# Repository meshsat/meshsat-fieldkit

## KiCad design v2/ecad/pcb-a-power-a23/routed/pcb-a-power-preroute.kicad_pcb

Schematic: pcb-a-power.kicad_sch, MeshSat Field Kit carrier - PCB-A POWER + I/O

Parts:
C1, C2: 47u 25V; C_1206_3216Metric
C3, C29, C30, C35, C36, C41, C42, C47, C48, C54, C120: 10u 25V 1210; C_1210_3225Metric
C4, C19: 1u; C_0603_1608Metric
C5, C26, C53, C57, C68, C75, C86, C98, C100, C102, C121: 10n; C_0603_1608Metric
C6, C58, C69, C76, C87: 100p; C_0603_1608Metric
C7, C59, C70, C77, C88: 47n; C_0603_1608Metric
C8, C60, C71, C78, C89: 4.7u; C_0805_2012Metric
C9, C10, C16, C17, C61, C62, C72, C73, C79, C80, C90, C91: 100n 25V; C_0603_1608Metric
C11, C12, C83, C84, C85: 10u 100V X7R 1210; C_1210_3225Metric
C13, C14, C15, C63, C64, C65, C66, C67, C74, C81, C82, C92, C108, C109, C110, C111, C116, C117, C118, C119: 10u 50V X7R 1210; C_1210_3225Metric
C18: 3.3u; C_0805_2012Metric
C20, C21, C22: 10u 35V 1210; C_1210_3225Metric
C23, C24, C25: 22u 25V 1210; C_1210_3225Metric
C27: 1n; C_0603_1608Metric
C28, C34, C40, C46, C52, C93, C95, C99, C101, C103, C104, C106, C107, C122: 100n; C_0603_1608Metric
C31, C32, C33, C37, C38, C39, C43, C44, C45, C49, C50, C51, C55, C56: 22u 10V X7R 1210; C_1210_3225Metric
C94: 220n; C_0603_1608Metric
C96, C97: 330p; C_0603_1608Metric
C112, C113, C114, C115: 3.3n; C_0603_1608Metric
D1: SMCJ18A (VBAT clamp); D_SMC; LCSC C374030
D2: SMCJ40A (VIN_RAW clamp behind E6's filter: 40 V s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; D_SMC; LCSC C224052
D3: SMBJ5.0A; D_SMB
D4: SMBJ18A (VBUS clamp at the outlet); D_SMB
F1: 25 A mini blade (Keystone 3568 holder): pack node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; Fuseholder_Blade_Mini_Keystone_3568
J_5V_DEV: USB device rail to B16 (JST-VH): + -; JST_VH_B2P-VH_1x02_P3.96mm_Vertical; LCSC C274411
J_5V_S1: slot 1 5.1 V rail to B16 (JST-VH, 16 AWG): + -; JST_VH_B2P-VH_1x02_P3.96mm_Vertical; LCSC C274411
J_5V_S2: slot 2 5.1 V rail to B16 (JST-VH, 16 AWG): + -; JST_VH_B2P-VH_1x02_P3.96mm_Vertical; LCSC C274411
J_5V_S3: slot 3 5.1 V rail to B16 (JST-VH, 16 AWG): + -; JST_VH_B2P-VH_1x02_P3.96mm_Vertical; LCSC C274411
J_54V: 54 V to the PoE injector on B16 (JST-VH): + -; JST_VH_B2P-VH_1x02_P3.96mm_Vertical; LCSC C274411
J_AB1: A-B interconnect (IDC 2x13, top side) to B16's un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; IDC-Header_2x13_P2.54mm_Vertical_NarrowPad
J_AB2: A-B wall-port ribbon (IDC 2x5): the wall USB pair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; IDC-Header_2x05_P2.54mm_Vertical_NarrowPad
J_BM1, J_BM2, J_BM3, J_BM4, J_BM5, J_BM6, J_BM7, J_BM8, J_BM9, J_BM10, J_BM11: SMP-MAX slide-on receptacle R222M00720 (underside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; Radiall_SMPMAX_R222M00720
J_CN1, J_CN2, J_CN3, J_CN4: 9 A spring pin, pack return (Mill-Max 0858 class,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; Mill-Max_0858_power_pin
J_CP1, J_CP2, J_CP3, J_CP4: 9 A spring pin, CELL+ (Mill-Max 0858 class, dock 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; Mill-Max_0858_power_pin
J_DOCK: spring pins to the dock block (2x6, Preci-Dip 813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; PogoPins_2x6
J_HEAT: JST-XH 1x2 socket: the heater mat under the 2590 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; JST_XH_B2B-XH-A_1x02_P2.50mm_Vertical; LCSC C265283
J_HF: 12.0 V to the QMX HF unit in its lid tray (JST-VH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; JST_VH_B2P-VH_1x02_P3.96mm_Vertical; LCSC C274411
J_MAINSW: JST-XH 1x2 socket: the MAIN button lead from the 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; JST_XH_B2B-XH-A_1x02_P2.50mm_Vertical; LCSC C265283
J_MEZZ1: D8 mezzanine harness (IDC 2x8): its USB pair, the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; IDC-Header_2x08_P2.54mm_Vertical_NarrowPad
J_MEZZ_PWR1: D8 mezzanine 5 V (JST-VH): + -; JST_VH_B2P-VH_1x02_P3.96mm_Vertical; LCSC C274411
J_MON: monitor supply lead to the Xenarc (JST-VH): + -; JST_VH_B2P-VH_1x02_P3.96mm_Vertical; LCSC C274411
J_PA: 13.8 V to the PA module on the face plate (JST-VH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; JST_VH_B2P-VH_1x02_P3.96mm_Vertical; LCSC C274411
J_PRE1: pre-charge pin, longer, mates first (32.24 AX); Mill-Max_0858_power_pin
J_RF1, J_RF2, J_RF3, J_RF4, J_RF5, J_RF6, J_RF7, J_RF8, J_RF9, J_RF10, J_RF11: SMA jack, Amphenol 132134-11 vertical (pigtail to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; SMA_Amphenol_132134-11_Vertical; LCSC C3174425
J_USBC_OUT: wall USB-C outlet, power side (pigtail header): V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; PinHeader_1x05_P2.54mm_Vertical
J_USBW: JST-PH 1x4 socket: the wall USB-C data pair to B1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; JST_PH_B4B-PH-K_1x04_P2.00mm_Vertical; LCSC C131334
L1: 10uH XAL1010-103ME (Isat 14 A); L_Coilcraft_XAL1010-XXX
L2: 3.3uH XAL6030-332ME (Isat 12.2 A); L_Coilcraft_XAL6060-XXX
L3, L4, L5, L6: 4.7uH XAL6060-472ME (Isat 11 A); L_Coilcraft_XAL6060-XXX
L7: 4.7uH XAL4030-472ME; L_Coilcraft_XAL4030-XXX
L8: 6.8uH XAL1010-682ME (Isat 17 A); L_Coilcraft_XAL1010-XXX
L9, L11: 6.8uH XAL1010-682ME; L_Coilcraft_XAL1010-XXX
L10: 22uH XAL1010-223ME (Isat 9 A); L_Coilcraft_XAL1010-XXX
Q1: 2N7002: panel controller high = pull KILL low = p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; SOT-23
Q2, Q3, Q4, Q5, Q17, Q18, Q19, Q20: CSD19532Q5B 100 V N-FET (4.6 mOhm at VGS 6 V, Pow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; PowerPAK_SO-8_Single; LCSC C473333
Q6: 2N7002: CHG_INHIBIT high = ILIM_HIZ low = charger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; SOT-23
Q7, Q8, Q9, Q10, Q11, Q12, Q13, Q14, Q15, Q16, Q21, Q22, Q23, Q24, Q25, Q26: CSD18510Q5B 40 V N-FET; PowerPAK_SO-8_Single
Q27: CSD18510Q5B 40 V N-FET (VBUS switch); PowerPAK_SO-8_Single
R1: 10R 2W 2512; R_2512_6332Metric
R2, R3, R4, R5, R13, R21, R30, R34, R38, R42, R57, R73, R102, R103, R104, R111, R112, R113, R114, R116, R118, R123, R128, R143, R145: 100k; R_0603_1608Metric
R6: 240k 1%; R_0603_1608Metric
R7, R15, R29, R33, R37, R41, R49, R51, R59, R61, R67, R75, R125, R134: 10k 1%; R_0603_1608Metric
R8, R52, R62, R68, R78: 40.2k (300 kHz); R_0603_1608Metric
R9, R53, R63, R69, R79: 30k (slope); R_0603_1608Metric
R10, R22, R23, R25, R44, R54, R64, R70, R80, R91, R95, R99, R110, R117, R142: 10k; R_0603_1608Metric
R11, R65, R81, R138: 10mOhm 1% 2512 (ISNS); R_2512_6332Metric
R12, R56, R122, R127: 5mOhm 1% 2512 (CS); R_2512_6332Metric
R14, R58, R74, R124, R133: 62k 1%; R_0603_1608Metric
R16: 10mOhm 1% 2512 (RAC, input current sense); R_2512_6332Metric
R17: 5mOhm 1% 2512 (RSR, charge current sense); R_2512_6332Metric
R18, R146, R147, R148, R149: 10R; R_0603_1608Metric
R19: 16.5k 1%; R_0603_1608Metric
R20: 34.8k 1%; R_0603_1608Metric
R24: 10k (PSYS load); R_0603_1608Metric
R26: 60.4k 1% (CELL_BATPRESZ: 4S per Table, from VDDA); R_0603_1608Metric
R27: 40.2k 1%; R_0603_1608Metric
R28, R32, R36, R40: 53.6k 1%; R_0603_1608Metric
R31, R35, R39, R43: 5mOhm 1% 2512 (shunt); R_2512_6332Metric
R45, R46, R47, R115: 68k (RT: 500 kHz); R_0603_1608Metric
R48: 31.6k 1%; R_0603_1608Metric
R50: 162k 1%; R_0603_1608Metric
R55: 2mOhm 1% 2512 (ISNS); R_2512_6332Metric
R60: 140k 1%; R_0603_1608Metric
R66: 665k 1%; R_0603_1608Metric
R71: 20mOhm 1% 2512 (ISNS); R_2512_6332Metric
R72: 10mOhm 1% 2512 (CS); R_2512_6332Metric
R76: 105k 1%; R_0603_1608Metric
R77: 20k 1% (R_FBL); R_0603_1608Metric
R90: 750R 1% (ILM: 1.2 A); R_0603_1608Metric
R92, R96, R100: 100k 1%; R_0603_1608Metric
R93, R97, R101: 10k 1% (OVLO); R_0603_1608Metric
R94: 909R 1% (ILM: 1.0 A); R_0603_1608Metric
R98: 453R 1% (ILM: 2.0 A); R_0603_1608Metric
R119, R120, R121, R126, R135: 100k (MODE: CCM); R_0603_1608Metric
R129, R130, R131, R132: 22k; R_0603_1608Metric
R136: 21.0k 1% (R_FBL2: 9 V when CTL2 is low); R_0603_1608Metric
R137: 14.0k 1% (R_FBL1: 15 V when CTL1 is low too); R_0603_1608Metric
R139: 43R 1W 2512 (DSCG); R_2512_6332Metric
R140: 1M (GD to VPWR, 9.1.3); R_0603_1608Metric
R141: 698k; R_0603_1608Metric
TP3: EXP2_SP3; TestPoint_Pad_D1.5mm
TP4: EXP2_SP4; TestPoint_Pad_D1.5mm
TP5: EXP2_SP5; TestPoint_Pad_D1.5mm
TP6: EXP2_SP6; TestPoint_Pad_D1.5mm
TP7: EXP2_SP7; TestPoint_Pad_D1.5mm
TP8: EXP2_SP8; TestPoint_Pad_D1.5mm
TP9: VBAT; TestPoint_Pad_D1.5mm
TP10: GND; TestPoint_Pad_D1.5mm
TP11: +3V3; TestPoint_Pad_D1.5mm
TP12: VBUS20; TestPoint_Pad_D1.5mm
TP13: VIN_RAW; TestPoint_Pad_D1.5mm
TP14: CELL+; TestPoint_Pad_D1.5mm
TP15: EMCON_HW; TestPoint_Pad_D1.5mm
TP16: RAIL_EN; TestPoint_Pad_D1.5mm
TP17: SDA; TestPoint_Pad_D1.5mm
TP18: SCL; TestPoint_Pad_D1.5mm
TP19: IADPT; TestPoint_Pad_D1.5mm
TP20: IBAT; TestPoint_Pad_D1.5mm
TP21: DOCK_SPARE; TestPoint_Pad_D1.5mm
TP22: REGN; TestPoint_Pad_D1.5mm
TP23: EXP2_SPA; TestPoint_Pad_D1.5mm
TP24: EXP2_SPB; TestPoint_Pad_D1.5mm
TP25: EXP2_SPC; TestPoint_Pad_D1.5mm
TP26: EXP2_SPD; TestPoint_Pad_D1.5mm
TP27: AB_SPARE; TestPoint_Pad_D1.5mm
U1: LTC2954CTS8-1 push-button on/off controller; TSOT-23-8; LCSC C683782
U2: LM5176PWPR buck-boost controller, VBUS20 from VIN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; HTSSOP-28-1EP_4.4x9.7mm_P0.65mm_EP2.85x5.4mm; LCSC C442493
U3: BQ25731RSNR 1 to 5 cell buck-boost charger, 4S fr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; QFN-32-1EP_4x4mm_P0.4mm_EP2.65x2.65mm; LCSC C2871872
U4: AP64500SP-13 5 A buck, 5.1 V rail +5V_S1; SOIC-8-1EP_3.9x4.9mm_P1.27mm_EP2.29x3mm; LCSC C2070920
U5: AP64500SP-13 5 A buck, 5.1 V rail +5V_S2; SOIC-8-1EP_3.9x4.9mm_P1.27mm_EP2.29x3mm; LCSC C2070920
U6: AP64500SP-13 5 A buck, 5.1 V rail +5V_S3; SOIC-8-1EP_3.9x4.9mm_P1.27mm_EP2.29x3mm; LCSC C2070920
U7: AP64500SP-13 5 A buck, 5.1 V rail +5V_DEV; SOIC-8-1EP_3.9x4.9mm_P1.27mm_EP2.29x3mm; LCSC C2070920
U8: INA226 rail monitor +5V_S1; VSSOP-10_3x3mm_P0.5mm; LCSC C49851
U9: INA226 rail monitor +5V_S2; VSSOP-10_3x3mm_P0.5mm; LCSC C49851
U10: INA226 rail monitor +5V_S3; VSSOP-10_3x3mm_P0.5mm; LCSC C49851
U11: INA226 rail monitor +5V_DEV; VSSOP-10_3x3mm_P0.5mm; LCSC C49851
U12: TPS62933DRLR 3 A buck, 3.3 V logic; SOT-583-8; LCSC C3200405
U13: LM5176PWPR buck-boost controller, +13V8_PA from V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; HTSSOP-28-1EP_4.4x9.7mm_P0.65mm_EP2.85x5.4mm; LCSC C442493
U14: INA226 PA rail monitor (0x46); VSSOP-10_3x3mm_P0.5mm; LCSC C49851
U15: LM5176PWPR buck-boost controller, +12V_HF from VB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; HTSSOP-28-1EP_4.4x9.7mm_P0.65mm_EP2.85x5.4mm; LCSC C442493
U16: LM5176PWPR buck-boost controller, +54V_POE from V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; HTSSOP-28-1EP_4.4x9.7mm_P0.65mm_EP2.85x5.4mm; LCSC C442493
U17: INA226 PoE rail monitor (0x47); VSSOP-10_3x3mm_P0.5mm; LCSC C49851
U18: TPS25740ARGER USB-C PD source controller, 45 W ou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; QFN-24-1EP_4x4mm_P0.5mm_EP2.5x2.5mm; LCSC C544309
U19: LM5176PWPR buck-boost controller, PD_VPWR from VB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; HTSSOP-28-1EP_4.4x9.7mm_P0.65mm_EP2.85x5.4mm; LCSC C442493
U21: TPS259631DDAR eFuse VBAT -> VMON (750R 1% (ILM: 1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; SOIC-8-1EP_3.9x4.9mm_P1.27mm_EP2.29x3mm; LCSC C2155778
U22: TPS259631DDAR eFuse VBAT -> VHEAT (909R 1% (ILM: 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; SOIC-8-1EP_3.9x4.9mm_P1.27mm_EP2.29x3mm; LCSC C2155778
U23: TPS259631DDAR eFuse +5V_DEV -> +5V_D8 (453R 1% (I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; SOIC-8-1EP_3.9x4.9mm_P1.27mm_EP2.29x3mm; LCSC C2155778
U26: SN74LVC08APWR quad AND: EMCON gates for the PA ra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; TSSOP-14_4.4x5mm_P0.65mm; LCSC C465737
U27: PCA9555PW (0x21): enables and status; TSSOP-24_4.4x7.8mm_P0.65mm; LCSC C2864778
U28: PCA9555PW (0x24): power-good lines, spares; TSSOP-24_4.4x7.8mm_P0.65mm; LCSC C2864778
U29: USBLC6-2SC6; SOT-23-6; LCSC C7519

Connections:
+3V3: C55.1, C56.1, C104.1, C106.1, C107.1, D3.1 (A1), J_MEZZ1.13, L7.2, R3.2, R13.2, R22.2, R23.2, R44.2, R48.1, R57.2, R73.2, R91.2, R95.2, R99.2, R110.2, R117.2, R123.2, R128.2, R142.2, TP11.1, U8.6 (+3V3), U9.2 (+3V3), U9.6 (+3V3), U10.1 (+3V3), U10.6 (+3V3), U11.1 (+3V3), U11.2 (+3V3), U11.6 (+3V3), U14.1 (+3V3), U14.6 (+3V3), U17.1 (+3V3), U17.6 (+3V3), U26.14 (+3V3), U27.21 (A0), U27.24 (VDD), U28.3 (A2), U28.24 (VDD)
/+5V_D8: J_MEZZ_PWR1.1, U23.5 (+5V_D8)
/+5V_DEV: C49.1, C50.1, C51.1, C103.1, J_5V_DEV.1, R40.1, R43.2, R100.1, U11.8 (+5V_DEV), U11.9 (+5V_DEV), U18.17 (+5V_DEV), U23.4 (+5V_DEV), U29.5 (VBUS)
/+5V_S1: C31.1, C32.1, C33.1, J_5V_S1.1, R28.1, R31.2, U8.8 (+5V_S1), U8.9 (+5V_S1)
/+5V_S2: C37.1, C38.1, C39.1, J_5V_S2.1, R32.1, R35.2, U9.8 (+5V_S2), U9.9 (+5V_S2)
/+5V_S3: C43.1, C44.1, C45.1, J_5V_S3.1, R36.1, R39.2, U10.8 (+5V_S3), U10.9 (+5V_S3)
/+12V_HF: C109.1, C110.1, C111.1, J_HF.1, R60.1, R65.2, U15.12 (+12V_HF), U15.13 (+12V_HF), U15.24 (+12V_HF)
/+13V8_PA: C65.1, C66.1, C67.1, J_PA.1, R50.1, R55.2, U13.12 (+13V8_PA), U13.13 (+13V8_PA), U13.24 (+13V8_PA), U14.8 (+13V8_PA), U14.9 (+13V8_PA)
/+54V_POE: C83.1, C84.1, C85.1, J_54V.1, R66.1, R71.2, U16.12 (+54V_POE), U16.13 (+54V_POE), U17.9 (+54V_POE)
/AB_SPARE: J_MEZZ1.16, TP27.1
/B33_BST: C52.1, U12.6 (B33_BST)
/B33_FB: R48.2, R49.1, U12.8 (B33_FB)
/B33_SS: C53.1, U12.7 (B33_SS)
/B33_SW: C52.2, L7.1, U12.5 (B33_SW)
/CHG_ILIM: Q6.3 (D), R19.2, R20.1, U3.6 (CHG_ILIM)
/CHG_INHIBIT: Q6.1 (G), R21.1, U27.4 (IO0_0)
/CHRG_OK: R22.1, U3.4 (CHRG_OK), U27.13 (IO1_0)
/CH_BTST1: C16.1, U3.30 (CH_BTST1)
/CH_BTST2: C17.1, U3.25 (CH_BTST2)
/CH_CELL: R26.2, R27.1, U3.18 (CH_CELL)
/CH_COMP1: R25.1, U3.16 (CH_COMP1)
/CH_COMP1C: C26.1, R25.2
/CH_COMP2: C27.1, U3.17 (CH_COMP2)
/CH_HIDRV1: Q7.4 (CH_HIDRV1), U3.31 (CH_HIDRV1)
/CH_HIDRV2: Q10.4 (CH_HIDRV2), U3.24 (CH_HIDRV2)
/CH_LODRV1: Q8.4 (CH_LODRV1), U3.29 (CH_LODRV1)
/CH_LODRV2: Q9.4 (CH_LODRV2), U3.26 (CH_LODRV2)
/CH_SW1: C16.2, L2.1, Q7.1 (CH_SW1), Q7.2 (CH_SW1), Q7.3 (CH_SW1), Q8.5 (CH_SW1), U3.32 (CH_SW1)
/CH_SW2: C17.2, L2.2, Q9.5 (CH_SW2), Q10.1 (CH_SW2), Q10.2 (CH_SW2), Q10.3 (CH_SW2), U3.23 (CH_SW2)
/CH_VDDA: C19.1, R18.2, R26.1, U3.7 (CH_VDDA)
/D8_EN: R113.1, U23.3 (D8_EN), U27.7 (IO0_3)
/D8_FLT: R99.1, U23.6 (D8_FLT), U27.17 (IO1_4)
/DEV_EN: R42.1, U7.3 (DEV_EN), U27.11 (IO0_7)
/DOCK_SPARE: J_DOCK.12, TP21.1, U27.18 (IO1_5)
/EMCON_HW: J_AB1.15, R102.1, TP15.1, U26.1 (EMCON_HW), U26.4 (EMCON_HW)
/EXP2_SP3: TP3.1, U28.15 (IO1_2)
/EXP2_SP4: TP4.1, U28.16 (IO1_3)
/EXP2_SP5: TP5.1, U28.17 (IO1_4)
/EXP2_SP6: TP6.1, U28.18 (IO1_5)
/EXP2_SP7: TP7.1, U28.19 (IO1_6)
/EXP2_SP8: TP8.1, U28.20 (IO1_7)
/EXP2_SPA: TP23.1, U28.4 (IO0_0)
/EXP2_SPB: TP24.1, U28.5 (IO0_1)
/EXP2_SPC: TP25.1, U28.6 (IO0_2)
/EXP2_SPD: TP26.1, U28.7 (IO0_3)
/EXP_INT: J_AB1.13, J_MEZZ1.12, R110.1, U27.1 (~INT), U28.1 (~INT)
/FE_BOOT1: C9.1, U2.26 (FE_BOOT1)
/FE_BOOT2: C10.1, U2.20 (FE_BOOT2)
/FE_COMP: C6.1, R10.1, U2.9 (FE_COMP)
/FE_COMPC: C5.1, R10.2
/FE_CS: Q3.1 (FE_CS), Q3.2 (FE_CS), Q3.3 (FE_CS), Q4.1 (FE_CS), Q4.2 (FE_CS), Q4.3 (FE_CS), R12.1, U2.16 (FE_CS)
/FE_EN: R14.2, R15.1, U2.1 (FE_EN)
/FE_FB: R6.2, R7.1, U2.11 (FE_FB)
/FE_HDRV1: Q2.4 (FE_HDRV1), U2.27 (FE_HDRV1)
/FE_HDRV2: Q5.4 (FE_HDRV2), U2.19 (FE_HDRV2)
/FE_LDRV1: Q3.4 (FE_LDRV1), U2.25 (FE_LDRV1)
/FE_LDRV2: Q4.4 (FE_LDRV2), U2.21 (FE_LDRV2)
/FE_MODE: R119.1, U2.4 (FE_MODE)
/FE_OUT: Q5.5 (FE_OUT), R11.1, U2.14 (FE_OUT)
/FE_PGOOD: R13.1, U2.17 (FE_PGOOD), U27.20 (IO1_7)
/FE_RT: R8.1, U2.6 (FE_RT)
/FE_SLOPE: R9.1, U2.7 (FE_SLOPE)
/FE_SS: C7.1, U2.8 (FE_SS)
/FE_SW1: C9.2, L1.1, Q2.1 (FE_SW1), Q2.2 (FE_SW1), Q2.3 (FE_SW1), Q3.5 (FE_SW1), U2.28 (FE_SW1)
/FE_SW2: C10.2, L1.2, Q4.5 (FE_SW2), Q5.1 (FE_SW2), Q5.2 (FE_SW2), Q5.3 (FE_SW2), U2.18 (FE_SW2)
/FE_VCC: C8.1, R119.2, U2.23 (FE_VCC)
/HEAT_EN: R112.1, U22.3 (HEAT_EN), U27.6 (IO0_2)
/HEAT_FLT: R95.1, U22.6 (HEAT_FLT), U27.16 (IO1_3)
/HF_BOOT1: C72.1, U15.26 (HF_BOOT1)
/HF_BOOT2: C73.1, U15.20 (HF_BOOT2)
/HF_COMP: C69.1, R64.1, U15.9 (HF_COMP)
/HF_COMPC: C68.1, R64.2
/HF_CS: Q16.1 (HF_CS), Q16.2 (HF_CS), Q16.3 (HF_CS), Q23.1 (HF_CS), Q23.2 (HF_CS), Q23.3 (HF_CS), R122.1, U15.16 (HF_CS)
/HF_EN: R124.1, R124.2, R125.1, U15.1 (HF_EN), U26.6 (HF_EN)
/HF_FB: R60.2, R61.1, U15.11 (HF_FB)
/HF_HDRV1: Q15.4 (HF_HDRV1), U15.27 (HF_HDRV1)
/HF_HDRV2: Q24.4 (HF_HDRV2), U15.19 (HF_HDRV2)
/HF_LDRV1: Q16.4 (HF_LDRV1), U15.25 (HF_LDRV1)
/HF_LDRV2: Q23.4 (HF_LDRV2), U15.21 (HF_LDRV2)
/HF_MODE: R126.1, U15.4 (HF_MODE)
/HF_OUT: Q24.5 (HF_OUT), R65.1, U15.14 (HF_OUT)
/HF_PGOOD: R123.1, U15.17 (HF_PGOOD), U28.10 (IO0_6)
/HF_RT: R62.1, U15.6 (HF_RT)
/HF_SLOPE: R63.1, U15.7 (HF_SLOPE)
/HF_SS: C70.1, U15.8 (HF_SS)
/HF_SW1: C72.2, L9.1, Q15.1 (HF_SW1), Q15.2 (HF_SW1), Q15.3 (HF_SW1), Q16.5 (HF_SW1), U15.28 (HF_SW1)
/HF_SW2: C73.2, L9.2, Q23.5 (HF_SW2), Q24.1 (HF_SW2), Q24.2 (HF_SW2), Q24.3 (HF_SW2), U15.18 (HF_SW2)
/HF_SW_EN: R104.1, U26.5 (HF_SW_EN), U27.10 (IO0_6)
/HF_VCC: C71.1, R126.2, U15.23 (HF_VCC)
/IADPT: TP19.1, U3.8 (IADPT)
/IBAT: TP20.1, U3.9 (IBAT)
/INA_ALERT: R44.1, U8.3 (INA_ALERT), U9.3 (INA_ALERT), U10.3 (INA_ALERT), U11.3 (INA_ALERT), U14.3 (INA_ALERT), U17.3 (INA_ALERT), U27.19 (IO1_6)
/KILL: Q1.3 (D), R4.1, U1.8 (KILL)
/MAIN_PB: J_MAINSW.1, U1.2 (MAIN_PB)
/MON_EN: R111.1, U21.3 (MON_EN), U27.5 (IO0_1)
/MON_FLT: R91.1, U21.6 (MON_FLT), U27.15 (IO1_2)
/PA_BOOT1: C61.1, U13.26 (PA_BOOT1)
/PA_BOOT2: C62.1, U13.20 (PA_BOOT2)
/PA_COMP: C58.1, R54.1, U13.9 (PA_COMP)
/PA_COMPC: C57.1, R54.2
/PA_CS: Q12.1 (PA_CS), Q12.2 (PA_CS), Q12.3 (PA_CS), Q13.1 (PA_CS), Q13.2 (PA_CS), Q13.3 (PA_CS), R56.1, U13.16 (PA_CS)
/PA_EN: J_MEZZ1.9, R58.1, R58.2, R59.1, U13.1 (PA_EN), U26.3 (PA_EN)
/PA_FB: R50.2, R51.1, U13.11 (PA_FB)
/PA_HDRV1: Q11.4 (PA_HDRV1), U13.27 (PA_HDRV1)
/PA_HDRV2: Q14.4 (PA_HDRV2), U13.19 (PA_HDRV2)
/PA_LDRV1: Q12.4 (PA_LDRV1), U13.25 (PA_LDRV1)
/PA_LDRV2: Q13.4 (PA_LDRV2), U13.21 (PA_LDRV2)
/PA_MODE: R120.1, U13.4 (PA_MODE)
/PA_OUT: Q14.5 (PA_OUT), R55.1, U13.14 (PA_OUT), U14.10 (PA_OUT)
/PA_PGOOD: R57.1, U13.17 (PA_PGOOD), U28.8 (IO0_4)
/PA_RT: R52.1, U13.6 (PA_RT)
/PA_SLOPE: R53.1, U13.7 (PA_SLOPE)
/PA_SS: C59.1, U13.8 (PA_SS)
/PA_SW1: C61.2, L8.1, Q11.1 (PA_SW1), Q11.2 (PA_SW1), Q11.3 (PA_SW1), Q12.5 (PA_SW1), U13.28 (PA_SW1)
/PA_SW2: C62.2, L8.2, Q13.5 (PA_SW2), Q14.1 (PA_SW2), Q14.2 (PA_SW2), Q14.3 (PA_SW2), U13.18 (PA_SW2)
/PA_SW_EN: R103.1, U26.2 (PA_SW_EN), U27.9 (IO0_5)
/PA_VCC: C60.1, R120.2, U13.23 (PA_VCC)
/PD_BOOT1: C90.1, U19.26 (PD_BOOT1)
/PD_BOOT2: C91.1, U19.20 (PD_BOOT2)
/PD_CC1: C96.1, J_USBC_OUT.2, U18.2 (PD_CC1)
/PD_CC2: C97.1, J_USBC_OUT.3, U18.3 (PD_CC2)
/PD_COMP: C87.1, R80.1, U19.9 (PD_COMP)
/PD_COMPC: C86.1, R80.2
/PD_CS: Q22.1 (PD_CS), Q22.2 (PD_CS), Q22.3 (PD_CS), Q25.1 (PD_CS), Q25.2 (PD_CS), Q25.3 (PD_CS), R127.1, U19.16 (PD_CS)
/PD_CTL1: R137.2, U18.6 (PD_CTL1)
/PD_CTL2: R136.2, U18.7 (PD_CTL2)
/PD_DSCG: R139.1, U18.24 (PD_DSCG)
/PD_DVDD: C94.1, U18.5 (PD_DVDD), U18.8 (PD_DVDD), U18.12 (PD_DVDD), U18.13 (PD_DVDD)
/PD_EN: R133.1, R133.2, R134.1, R143.1, U19.1 (PD_EN), U28.13 (IO1_0)
/PD_FB: R76.2, R77.1, R136.1, R137.1, U19.11 (PD_FB)
/PD_GD: R140.2, R141.1, U18.15 (PD_GD)
/PD_GDNG: Q27.4 (PD_GDNG), U18.22 (PD_GDNG)
/PD_HDRV1: Q21.4 (PD_HDRV1), U19.27 (PD_HDRV1)
/PD_HDRV2: Q26.4 (PD_HDRV2), U19.19 (PD_HDRV2)
/PD_LDRV1: Q22.4 (PD_LDRV1), U19.25 (PD_LDRV1)
/PD_LDRV2: Q25.4 (PD_LDRV2), U19.21 (PD_LDRV2)
/PD_MODE: R135.1, U19.4 (PD_MODE)
/PD_OUT: Q26.5 (PD_OUT), R81.1, U19.14 (PD_OUT)
/PD_PGOOD: R128.1, U19.17 (PD_PGOOD), U28.11 (IO0_7)
/PD_RT: R78.1, U19.6 (PD_RT)
/PD_SLOPE: R79.1, U19.7 (PD_SLOPE)
/PD_SS: C88.1, U19.8 (PD_SS)
/PD_SW: Q27.1 (PD_SW), Q27.2 (PD_SW), Q27.3 (PD_SW), R138.1, U18.19 (PD_SW), U18.23 (PD_SW)
/PD_SW1: C90.2, L11.1, Q21.1 (PD_SW1), Q21.2 (PD_SW1), Q21.3 (PD_SW1), Q22.5 (PD_SW1), U19.28 (PD_SW1)
/PD_SW2: C91.2, L11.2, Q25.5 (PD_SW2), Q26.1 (PD_SW2), Q26.2 (PD_SW2), Q26.3 (PD_SW2), U19.18 (PD_SW2)
/PD_UFP: R142.1, U18.11 (PD_UFP), U28.14 (IO1_1)
/PD_VAUX: C95.1, U18.14 (PD_VAUX), U18.16 (PD_VAUX)
/PD_VBUS: C120.1, D4.1 (A1), J_USBC_OUT.1, R138.2, R139.2, U18.21 (PD_VBUS)
/PD_VCC: C89.1, R135.2, U19.23 (PD_VCC)
/PD_VPWR: C117.1, C118.1, C119.1, Q27.5 (PD_VPWR), R76.1, R81.2, R140.1, U18.20 (PD_VPWR), U19.12 (PD_VPWR), U19.13 (PD_VPWR), U19.24 (PD_VPWR)
/PD_VTX: C93.1, U18.1 (PD_VTX)
/PI_KILL: J_AB1.10, Q1.1 (G), R5.1
/PI_SHDN_REQ: J_AB1.9, R3.1, U1.5 (PI_SHDN_REQ)
/POE_BOOT1: C79.1, U16.26 (POE_BOOT1)
/POE_BOOT2: C80.1, U16.20 (POE_BOOT2)
/POE_COMP: C76.1, R70.1, U16.9 (POE_COMP)
/POE_COMPC: C75.1, R70.2
/POE_CS: Q18.1 (POE_CS), Q18.2 (POE_CS), Q18.3 (POE_CS), Q19.1 (POE_CS), Q19.2 (POE_CS), Q19.3 (POE_CS), R72.1, U16.16 (POE_CS)
/POE_EN: R74.1, R74.2, R75.1, R114.1, U16.1 (POE_EN), U27.8 (IO0_4)
/POE_FB: R66.2, R67.1, U16.11 (POE_FB)
/POE_HDRV1: Q17.4 (POE_HDRV1), U16.27 (POE_HDRV1)
/POE_HDRV2: Q20.4 (POE_HDRV2), U16.19 (POE_HDRV2)
/POE_LDRV1: Q18.4 (POE_LDRV1), U16.25 (POE_LDRV1)
/POE_LDRV2: Q19.4 (POE_LDRV2), U16.21 (POE_LDRV2)
/POE_MODE: R121.1, U16.4 (POE_MODE)
/POE_OUT: Q20.5 (POE_OUT), R71.1, U16.14 (POE_OUT), U17.10 (POE_OUT)
/POE_PGOOD: R73.1, U16.17 (POE_PGOOD), U28.9 (IO0_5)
/POE_RT: R68.1, U16.6 (POE_RT)
/POE_SLOPE: R69.1, U16.7 (POE_SLOPE)
/POE_SS: C77.1, U16.8 (POE_SS)
/POE_SW1: C79.2, L10.1, Q17.1 (POE_SW1), Q17.2 (POE_SW1), Q17.3 (POE_SW1), Q18.5 (POE_SW1), U16.28 (POE_SW1)
/POE_SW2: C80.2, L10.2, Q19.5 (POE_SW2), Q20.1 (POE_SW2), Q20.2 (POE_SW2), Q20.3 (POE_SW2), U16.18 (POE_SW2)
/POE_VCC: C78.1, R121.2, U16.23 (POE_VCC)
/PRECHG: J_PRE1.1, R1.1
/PROCHOT: R23.1, U3.11 (PROCHOT), U27.14 (IO1_1)
/PSYS: R24.1, U3.10 (PSYS)
/RAIL_EN: R2.1, TP16.1, U1.6 (RAIL_EN), U12.2 (RAIL_EN)
/REGN: C18.1, R18.1, R19.1, TP22.1, U3.28 (REGN)
/RF_5G1: J_BM8.1 (In), J_RF8.1 (In)
/RF_5G2: J_BM9.1 (In), J_RF9.1 (In)
/RF_GNSS: J_BM4.1 (In), J_RF4.1 (In)
/RF_HF: J_BM2.1 (In), J_RF2.1 (In)
/RF_IRIDIUM: J_BM10.1 (In), J_RF10.1 (In)
/RF_LORA: J_BM11.1 (In), J_RF11.1 (In)
/RF_P2PA: J_BM6.1 (In), J_RF6.1 (In)
/RF_P2PB: J_BM7.1 (In), J_RF7.1 (In)
/RF_SDR: J_BM5.1 (In), J_RF5.1 (In)
/RF_VHF: J_BM1.1 (In), J_RF1.1 (In)
/RF_WIFI24: J_BM3.1 (In), J_RF3.1 (In)
/S1_BOOT: C28.1, U4.1 (S1_BOOT)
/S1_COMP: R129.1, U4.6 (S1_COMP)
/S1_COMPC: C112.1, R129.2
/S1_FB: R28.2, R29.1, U4.5 (S1_FB)
/S1_OUT: L3.2, R31.1, U8.10 (S1_OUT)
/S1_RT: R45.1, U4.4 (S1_RT)
/S1_SW: C28.2, L3.1, U4.8 (S1_SW)
/S2_BOOT: C34.1, U5.1 (S2_BOOT)
/S2_COMP: R130.1, U5.6 (S2_COMP)
/S2_COMPC: C113.1, R130.2
/S2_FB: R32.2, R33.1, U5.5 (S2_FB)
/S2_OUT: L4.2, R35.1, U9.10 (S2_OUT)
/S2_RT: R46.1, U5.4 (S2_RT)
/S2_SW: C34.2, L4.1, U5.8 (S2_SW)
/S3_BOOT: C40.1, U6.1 (S3_BOOT)
/S3_COMP: R131.1, U6.6 (S3_COMP)
/S3_COMPC: C114.1, R131.2
/S3_FB: R36.2, R37.1, U6.5 (S3_FB)
/S3_OUT: L5.2, R39.1, U10.10 (S3_OUT)
/S3_RT: R47.1, U6.4 (S3_RT)
/S3_SW: C40.2, L5.1, U6.8 (S3_SW)
/SCL: J_AB1.12, J_MEZZ1.11, TP18.1, U3.13 (SCL), U8.5 (SCL), U9.5 (SCL), U10.5 (SCL), U11.5 (SCL), U14.5 (SCL), U17.2 (SCL), U17.5 (SCL), U27.22 (SCL), U28.22 (SCL)
/SDA: J_AB1.11, J_MEZZ1.10, TP17.1, U3.12 (SDA), U8.4 (SDA), U9.4 (SDA), U10.4 (SDA), U11.4 (SDA), U14.2 (SDA), U14.4 (SDA), U17.4 (SDA), U27.23 (SDA), U28.23 (SDA)
/SD_BOOT: C46.1, U7.1 (SD_BOOT)
/SD_COMP: R132.1, U7.6 (SD_COMP)
/SD_COMPC: C115.1, R132.2
/SD_FB: R40.2, R41.1, U7.5 (SD_FB)
/SD_OUT: L6.2, R43.1, U11.10 (SD_OUT)
/SD_RT: R115.1, U7.4 (SD_RT)
/SD_SW: C46.2, L6.1, U7.8 (SD_SW)
/SHORE_INHIBIT: J_AB1.21, J_DOCK.8, R118.1
/SLOT_EN1: J_AB1.17, R30.1, U4.3 (SLOT_EN1)
/SLOT_EN2: J_AB1.18, R34.1, U5.3 (SLOT_EN2)
/SLOT_EN3: J_AB1.19, R38.1, U6.3 (SLOT_EN3)
/TR_APRS: J_AB1.14, J_MEZZ1.7, R116.1
/TX_INHIBIT_n: J_AB1.16, J_MEZZ1.8, R145.1
/U21_DVDT: C98.1, U21.2 (U21_DVDT)
/U21_ILM: R90.1, U21.7 (U21_ILM)
/U21_OVLO: R92.2, R93.1, U21.8 (U21_OVLO)
/U22_DVDT: C100.1, U22.2 (U22_DVDT)
/U22_ILM: R94.1, U22.7 (U22_ILM)
/U22_OVLO: R96.2, R97.1, U22.8 (U22_OVLO)
/U23_DVDT: C102.1, U23.2 (U23_DVDT)
/U23_ILM: R98.1, U23.7 (U23_ILM)
/U23_OVLO: R100.2, R101.1, U23.8 (U23_OVLO)
/USB_D8_N: J_AB1.2, J_MEZZ1.2
/USB_D8_P: J_AB1.1, J_MEZZ1.1
/USB_E6_N: J_AB1.26, J_DOCK.10
/USB_E6_P: J_AB1.25, J_DOCK.9
/USB_WALL_N: J_AB2.2, J_USBW.2, U29.3 (I/O2), U29.4 (I/O2)
/USB_WALL_P: J_AB2.1, J_USBW.1, U29.1 (I/O1), U29.6 (I/O1)
/VBAT: C1.1, C2.1, C3.1, C4.1, C29.1, C30.1, C35.1, C36.1, C41.1, C42.1, C47.1, C48.1, C54.1, C63.1, C64.1, C74.1, C81.1, C82.1, C92.1, C99.1, C101.1, C108.1, C116.1, D1.1 (A1), F1.2, Q11.5 (VBAT), Q15.5 (VBAT), Q17.5 (VBAT), Q21.5 (VBAT), R2.2, R4.2, R92.1, R96.1, TP9.1, U1.1 (VBAT), U4.2 (VBAT), U5.2 (VBAT), U6.2 (VBAT), U7.2 (VBAT), U12.3 (VBAT), U13.2 (VBAT), U13.3 (VBAT), U15.2 (VBAT), U15.3 (VBAT), U16.2 (VBAT), U16.3 (VBAT), U16.24 (VBAT), U19.2 (VBAT), U19.3 (VBAT), U21.4 (VBAT), U22.4 (VBAT)
/VHEAT: J_HEAT.1, U22.5 (VHEAT)
/VIN_RAW: C11.1, C12.1, D2.1 (A1), J_DOCK.1, J_DOCK.2, J_DOCK.3, J_DOCK.4, Q2.5 (VIN_RAW), R14.1, TP13.1, U2.2 (VIN_RAW), U2.3 (VIN_RAW)
/VMON: J_MON.1, U21.5 (VMON)
/ZEROIZE_HW: J_AB1.20, J_MEZZ1.15, R117.1
GND: C1.2, C2.2, C3.2, C4.2, C5.2, C6.2, C7.2, C8.2, C11.2, C12.2, C13.2, C14.2, C15.2, C18.2, C19.2, C20.2, C21.2, C22.2, C23.2, C24.2, C25.2, C26.2, C27.2, C29.2, C30.2, C31.2, C32.2, C33.2, C35.2, C36.2, C37.2, C38.2, C39.2, C41.2, C42.2, C43.2, C44.2, C45.2, C47.2, C48.2, C49.2, C50.2, C51.2, C53.2, C54.2, C55.2, C56.2, C57.2, C58.2, C59.2, C60.2, C63.2, C64.2, C65.2, C66.2, C67.2, C68.2, C69.2, C70.2, C71.2, C74.2, C75.2, C76.2, C77.2, C78.2, C81.2, C82.2, C83.2, C84.2, C85.2, C86.2, C87.2, C88.2, C89.2, C92.2, C93.2, C94.2, C95.2, C96.2, C97.2, C98.2, C99.2, C100.2, C101.2, C102.2, C103.2, C104.2, C106.2, C107.2, C108.2, C109.2, C110.2, C111.2, C112.2, C113.2, C114.2, C115.2, C116.2, C117.2, C118.2, C119.2, C120.2, D1.2 (A2), D2.2 (A2), D3.2 (A2), D4.2 (A2), J_5V_DEV.2, J_5V_S1.2, J_5V_S2.2, J_5V_S3.2, J_54V.2, J_AB1.3, J_AB1.4, J_AB1.5, J_AB1.6, J_AB1.7, J_AB1.8, J_AB1.22, J_AB1.23, J_AB1.24, J_AB2.3, J_AB2.4, J_AB2.5, J_AB2.6, J_AB2.7, J_AB2.8, J_AB2.9, J_AB2.10, J_BM1.2 (Ext), J_BM2.2 (Ext), J_BM3.2 (Ext), J_BM4.2 (Ext), J_BM5.2 (Ext), J_BM6.2 (Ext), J_BM7.2 (Ext), J_BM8.2 (Ext), J_BM9.2 (Ext), J_BM10.2 (Ext), J_BM11.2 (Ext), J_CN1.1, J_CN2.1, J_CN3.1, J_CN4.1, J_DOCK.5, J_DOCK.6, J_DOCK.7, J_DOCK.11, J_HEAT.2, J_HF.2, J_MAINSW.2, J_MEZZ1.3, J_MEZZ1.4, J_MEZZ1.5, J_MEZZ1.6, J_MEZZ1.14, J_MEZZ_PWR1.2, J_MON.2, J_PA.2, J_RF1.2 (Ext), J_RF2.2 (Ext), J_RF3.2 (Ext), J_RF4.2 (Ext), J_RF5.2 (Ext), J_RF6.2 (Ext), J_RF7.2 (Ext), J_RF8.2 (Ext), J_RF9.2 (Ext), J_RF10.2 (Ext), J_RF11.2 (Ext), J_USBC_OUT.4, J_USBC_OUT.5, J_USBW.3, J_USBW.4, Q1.2 (S), Q6.2 (S), Q8.1 (GND), Q8.2 (GND), Q8.3 (GND), Q9.1 (GND), Q9.2 (GND), Q9.3 (GND), R5.2, R7.2, R8.2, R9.2, R12.2, R15.2, R20.2, R21.2, R24.2, R27.2, R29.2, R30.2, R33.2, R34.2, R37.2, R38.2, R41.2, R42.2, R45.2, R46.2, R47.2, R49.2, R51.2, R52.2, R53.2, R56.2, R59.2, R61.2, R62.2, R63.2, R67.2, R68.2, R69.2, R72.2, R75.2, R77.2, R78.2, R79.2, R90.2, R93.2, R94.2, R97.2, R98.2, R101.2, R102.2, R103.2, R104.2, R111.2, R112.2, R113.2, R114.2, R115.2, R116.2, R118.2, R122.2, R125.2, R127.2, R134.2, R141.2, R143.2, R145.2, TP10.1, U1.4 (GND), U2.5 (GND), U2.10 (GND), U2.15 (GND), U2.22 (GND), U2.29 (GND), U3.5 (GND), U3.14 (GND), U3.27 (GND), U3.33 (GND), U4.7 (GND), U4.9 (GND), U5.7 (GND), U5.9 (GND), U6.7 (GND), U6.9 (GND), U7.7 (GND), U7.9 (GND), U8.1 (GND), U8.2 (GND), U8.7 (GND), U9.1 (GND), U9.7 (GND), U10.2 (GND), U10.7 (GND), U11.7 (GND), U12.4 (GND), U13.5 (GND), U13.10 (GND), U13.15 (GND), U13.22 (GND), U13.29 (GND), U14.7 (GND), U15.5 (GND), U15.10 (GND), U15.15 (GND), U15.22 (GND), U15.29 (GND), U16.5 (GND), U16.10 (GND), U16.15 (GND), U16.22 (GND), U16.29 (GND), U17.7 (GND), U18.4 (GND), U18.9 (GND), U18.10 (GND), U18.18 (GND), U18.25 (GND), U19.5 (GND), U19.10 (GND), U19.15 (GND), U19.22 (GND), U19.29 (GND), U21.1 (GND), U21.9 (GND), U22.1 (GND), U22.9 (GND), U23.1 (GND), U23.9 (GND), U26.7 (GND), U26.9 (GND), U26.10 (GND), U26.12 (GND), U26.13 (GND), U27.2 (A1), U27.3 (A2), U27.12 (VSS), U28.2 (A1), U28.12 (VSS), U28.21 (A0), U29.2 (GND)

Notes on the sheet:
PCB-A POWER + I/O A32
PACK NODE OVER THE DOCK BLOCK (32.56) | MAIN POWER CONTROL LTC2954 | FRONT END
PACK NODE OVER THE DOCK BLOCK (32.56): 9 A PINS, PRE-CHARGE, 25 A BLADE, DOCK SIGNAL PINS
MAIN POWER CONTROL LTC2954
FRONT END: LM5176 FROM THE 9 TO 36 V INPUT TO THE 20 V CHARGE BUS
page 1 of 11 MeshSat field kit V2, CERN-OHL-S-2.0 PROTOTYPE, nothing built 2026-09-17
spring pins to the dock block
25 A mini blade
SMCJ18A
9 A spring pin
pre-charge pin
LTC2954CTS8-1 push-button on/off c..
2N7002
JST-XH 1x2 socket
LM5176PWPR buck-boost controller
100k
40.2k
30k
10mOhm 1% 2512
5mOhm 1% 2512
10uH XAL1010-103ME
decoupling of U2
10u 100V
SMCJ40A
10u 50V
p10
p11
p4,10
p2,11
FRONT END | CHARGER BQ25731
FRONT END: LM5176 FROM THE 9 TO 36 V INPUT TO THE 20 V CHARGE BUS (continued)
CHARGER BQ25731: 4S FROM THE 20 V BUS INTO THE PACK NODE, I2C 0x6B
page 2 of 11 MeshSat field kit V2, CERN-OHL-S-2.0 PROTOTYPE, nothing built 2026-09-17
CSD19532Q5B 100 V N-FET
BQ25731RSNR 1 to 5 cell buck-boost..
60.4k 1%
10k
3.3uH XAL6030-332ME
10mOhm 1%
10u 35V

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
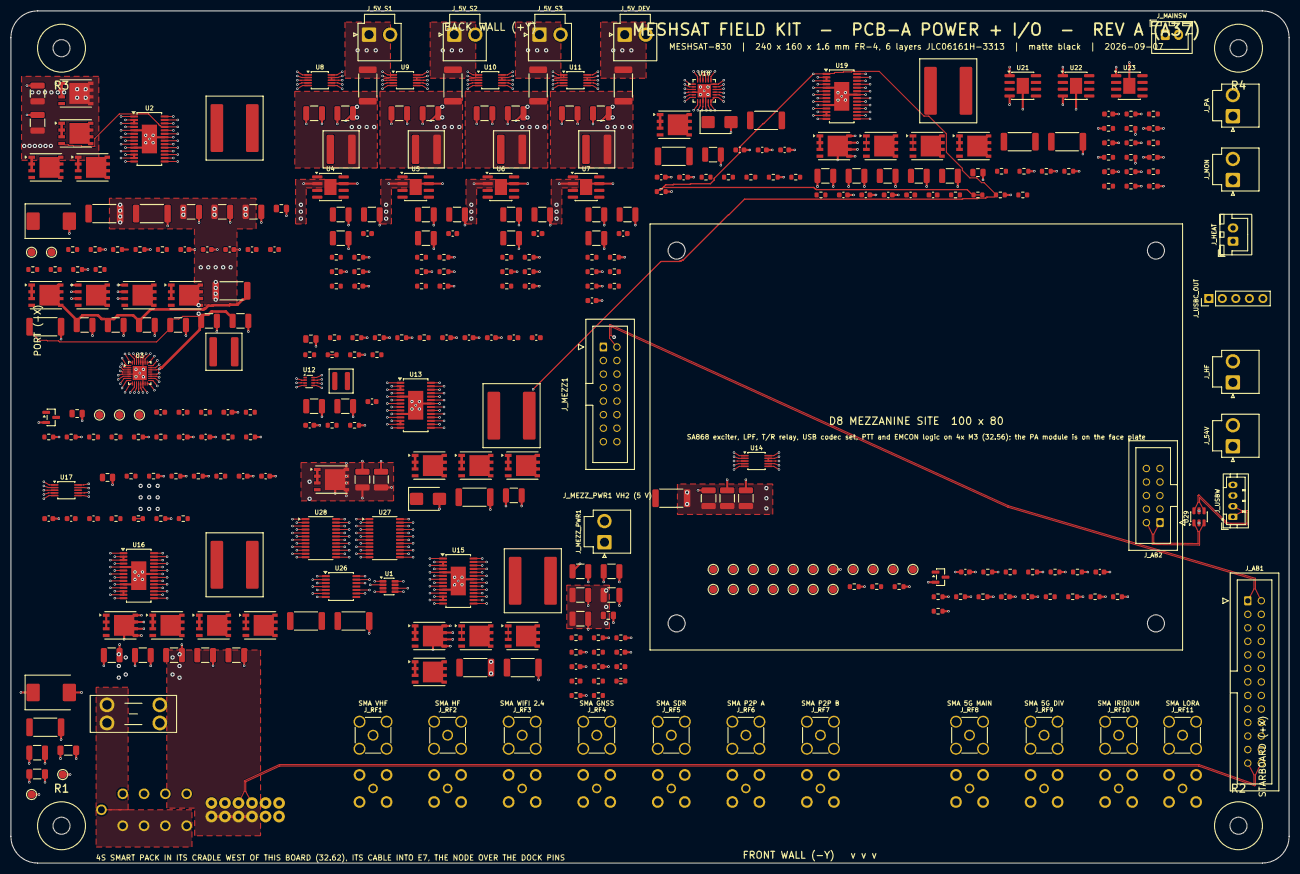
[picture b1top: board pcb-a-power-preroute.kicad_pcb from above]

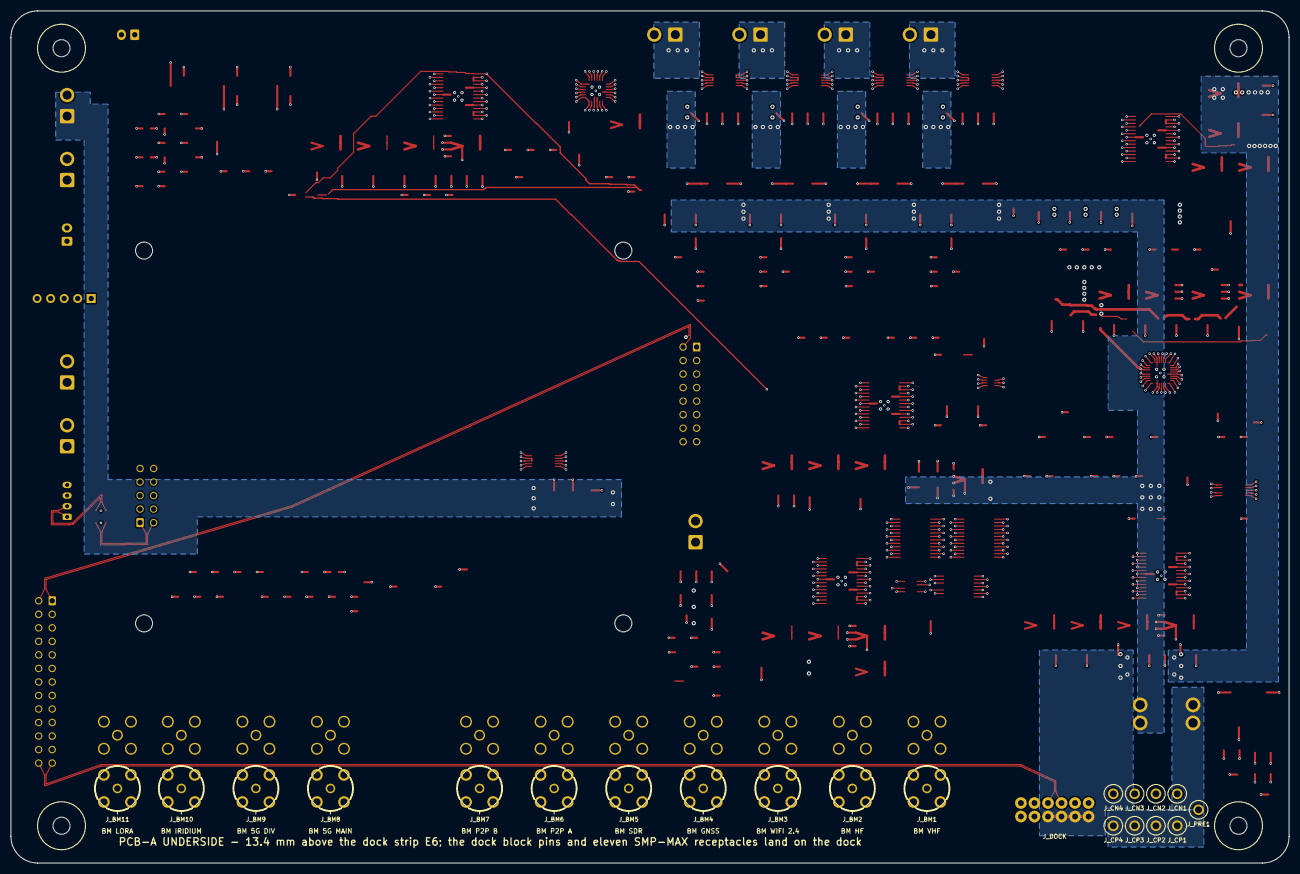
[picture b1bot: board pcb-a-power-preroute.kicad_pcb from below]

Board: 6 copper layers, 240.0 x 160.0 mm, 400 parts (21 on the bottom side), 250 nets.

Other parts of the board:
H1: M3 rod R1; MountingHole_3.2mm_M3
H2: M3 rod R2; MountingHole_3.2mm_M3
H3: M3 rod R3; MountingHole_3.2mm_M3
H4: M3 rod R4; MountingHole_3.2mm_M3
H5, H6, H7, H8: M3 standoff, mezzanine; MountingHole_3.2mm_M3

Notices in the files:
v2/ecad/pcb-a-power-a23/pcb-a-power.kicad_sch:
page 3 of 11 MeshSat field kit V2, CERN-OHL-S-2.0 PROTOTYPE, nothing built 2026-09-17
page 4 of 11 MeshSat field kit V2, CERN-OHL-S-2.0 PROTOTYPE, nothing built 2026-09-17
page 5 of 11 MeshSat field kit V2, CERN-OHL-S-2.0 PROTOTYPE, nothing built 2026-09-17
page 6 of 11 MeshSat field kit V2, CERN-OHL-S-2.0 PROTOTYPE, nothing built 2026-09-17
page 7 of 11 MeshSat field kit V2, CERN-OHL-S-2.0 PROTOTYPE, nothing built 2026-09-17
page 8 of 11 MeshSat field kit V2, CERN-OHL-S-2.0 PROTOTYPE, nothing built 2026-09-17
